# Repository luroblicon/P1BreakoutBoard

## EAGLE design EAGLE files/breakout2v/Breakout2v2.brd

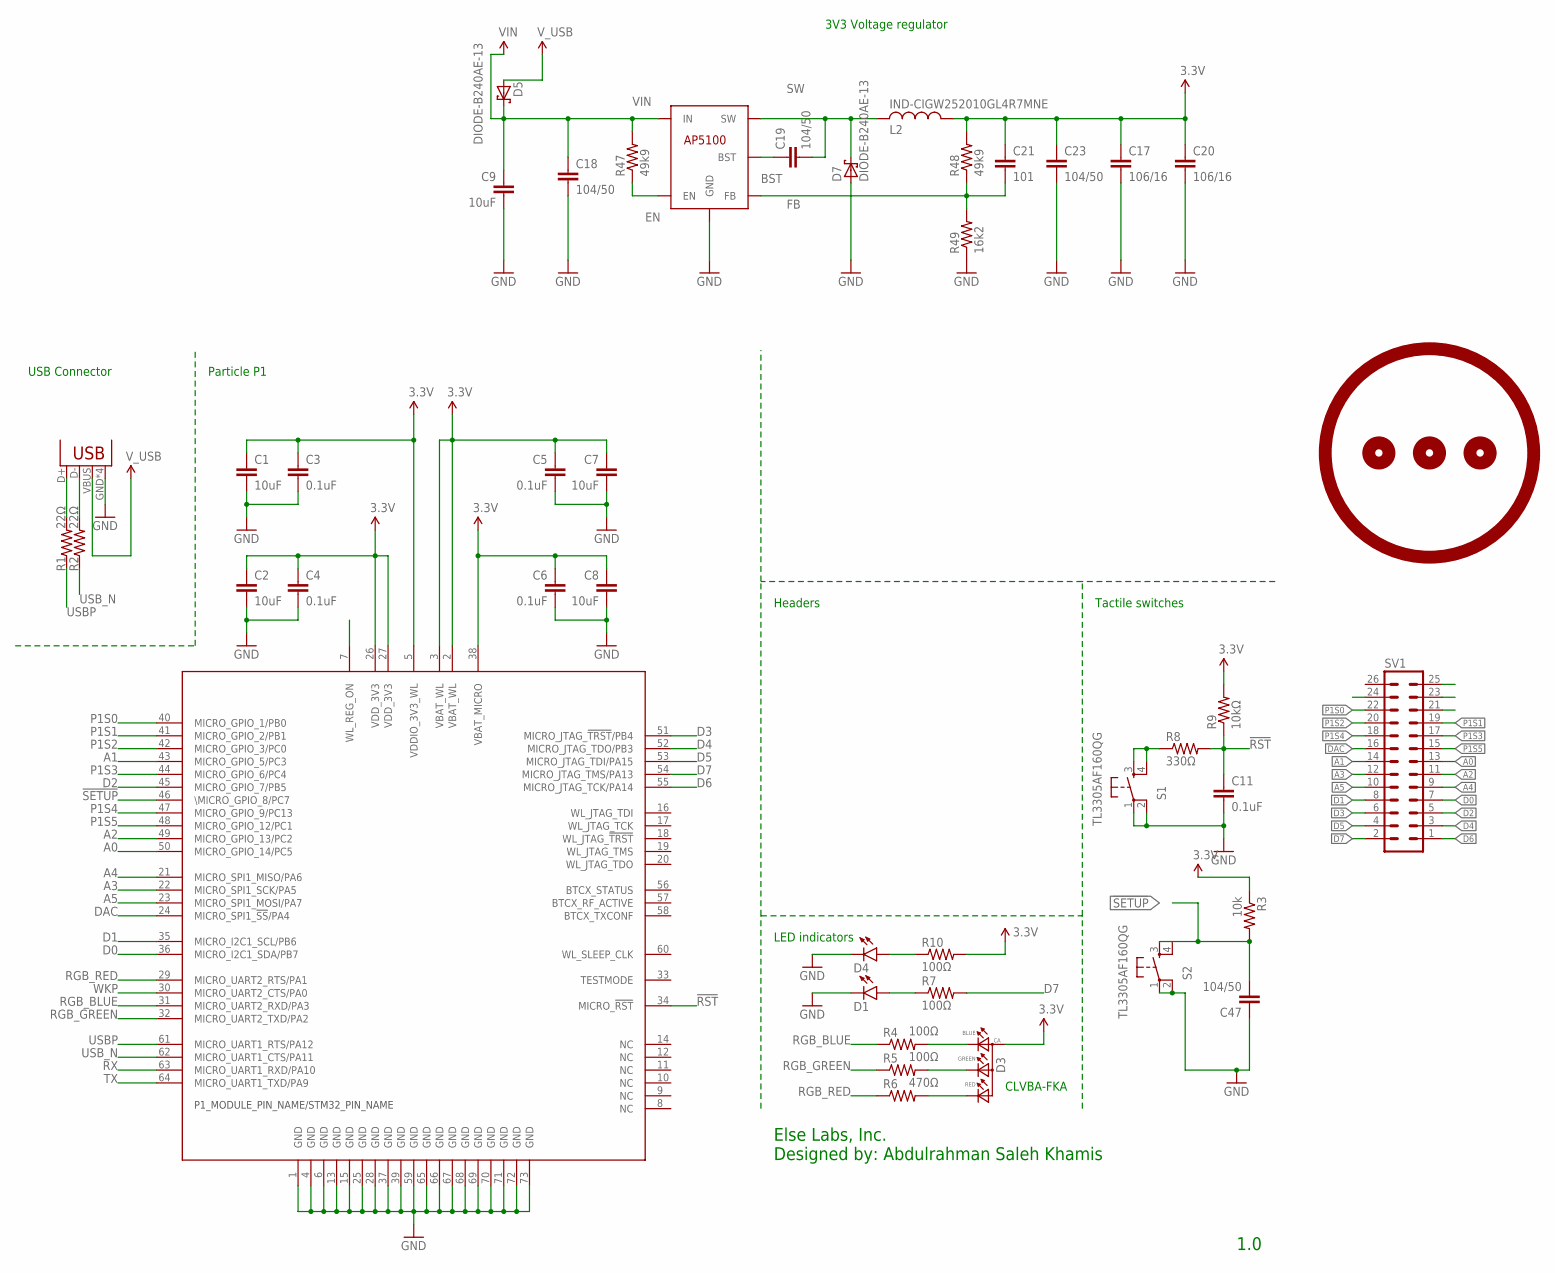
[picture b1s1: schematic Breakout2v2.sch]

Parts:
C1, C2, C7, C8, C9: 10uF; 0805
C3, C4, C5, C6, C11: 0.1uF; 0805
C17, C20: 106/16; C0805
C18, C19, C23, C47: 104/50; C0603
C21: 101; C0603
D1, D4: LED0603; LED-0603
D3: CLVBA-FKAPLCC; 4-PLCC
D5, D7: DIODE-B240AE-13; DO-214AC
IC5: SMSP-BUCK-AP5100; SOT23-6
JP1: USBUSB-MICROB-SLOT-HOLE; USB-MICROB-SLOT-HOLE
L2: IND-CIGW252010GL4R7MNE; L2520
R1, R2: 22Ω; 0805
R3: 10k; R0603
R4, R5, R7, R10: 100Ω; 0805
R6: 470Ω; 0805
R8: 330Ω; 0805
R9: 10kΩ; 0805
R47, R48: 49k9; R0603
R49: 16k2; R0603
S1, S2: TL3305AF160QG; TACTILE_SWITCH_SMD_4.5X4.5MM
SV1: MA13-2
U$1: LOGO
UC1: P1; WM-N-BM-14

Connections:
3.3V: C1.1, C2.1, C3.1, C4.1, C5.1, C6.1, C7.1, C8.1, C17.1, C20.1, C21.1, C23.1, D3.2 (ANODE), L2.P$1 (1), R3.1, R9.2, R10.2, R48.2, UC1.2 (VBAT_WL), UC1.3 (VBAT_WL), UC1.5 (VDDIO_3V3_WL), UC1.26 (VDD_3V3), UC1.27 (VDD_3V3), UC1.38 (VBAT_MICRO)
!RST: C11.1, R8.2, R9.1, UC1.34 (MICRO_!RST!)
!SETUP: C47.2, R3.2, S2.3, S2.4, UC1.46 (\MICRO_GPIO_8/PC7)
A0: SV1.13, UC1.50 (MICRO_GPIO_14/PC5)
A1: SV1.14, UC1.43 (MICRO_GPIO_5/PC3)
A2: SV1.11, UC1.49 (MICRO_GPIO_13/PC2)
A3: SV1.12, UC1.22 (MICRO_SPI1_SCK/PA5)
A4: SV1.9, UC1.21 (MICRO_SPI1_MISO/PA6)
A5: SV1.10, UC1.23 (MICRO_SPI1_MOSI/PA7)
BLR: D3.3 (BLUE), R4.2
BST: C19.1, IC5.1 (BST)
D0: SV1.7, UC1.36 (MICRO_I2C1_SDA/PB7)
D1: SV1.8, UC1.35 (MICRO_I2C1_SCL/PB6)
D2: SV1.5, UC1.45 (MICRO_GPIO_7/PB5)
D3: SV1.6, UC1.51 (MICRO_JTAG_!TRST!/PB4)
D4: SV1.3, UC1.52 (MICRO_JTAG_TDO/PB3)
D5: SV1.4, UC1.53 (MICRO_JTAG_TDI/PA15)
D6: SV1.1, UC1.55 (MICRO_JTAG_TCK/PA14)
D7: R7.2, SV1.2, UC1.54 (MICRO_JTAG_TMS/PA13)
DAC: SV1.16, UC1.24 (MICRO_SPI1_!SS!/PA4)
EN: IC5.4 (EN), R47.1
FB: C21.2, IC5.3 (FB), R48.1, R49.2
GND: C1.2, C2.2, C3.2, C4.2, C5.2, C6.2, C7.2, C8.2, C9.2, C11.2, C17.2, C18.2, C20.2, C23.2, C47.1, D1.C, D4.C, D7.A, IC5.2 (GND), JP1.GND, JP1.P$1 (GND), JP1.P$2 (GND), JP1.P$3 (GND), R49.1, S1.1, S1.2, S2.1, S2.2, UC1.1 (GND), UC1.4 (GND), UC1.6 (GND), UC1.13 (GND), UC1.15 (GND), UC1.25 (GND), UC1.28 (GND), UC1.37 (GND), UC1.39 (GND), UC1.59 (GND), UC1.65 (GND), UC1.66 (GND), UC1.67 (GND), UC1.68 (GND), UC1.69 (GND), UC1.70 (GND), UC1.71 (GND), UC1.72 (GND), UC1.73 (GND)
GRR: D3.4 (GREEN), R5.2
unnamed: JP1.D+, R1.2
unnamed: JP1.D-, R2.2
unnamed: D1.A, R7.1
unnamed: R8.1, S1.3, S1.4
unnamed: D4.A, R10.1
P1S0: SV1.22, UC1.40 (MICRO_GPIO_1/PB0)
P1S1: SV1.19, UC1.41 (MICRO_GPIO_2/PB1)
P1S2: SV1.20, UC1.42 (MICRO_GPIO_3/PC0)
P1S3: SV1.17, UC1.44 (MICRO_GPIO_6/PC4)
P1S4: SV1.18, UC1.47 (MICRO_GPIO_9/PC13)
P1S5: SV1.15, UC1.48 (MICRO_GPIO_12/PC1)
RER: D3.1 (RED), R6.2
RGB_BLUE: R4.1, UC1.31 (MICRO_UART2_RXD/PA3)
RGB_GREEN: R5.1, UC1.32 (MICRO_UART2_TXD/PA2)
RGB_RED: R6.1, UC1.29 (MICRO_UART2_RTS/PA1)
RX: UC1.63 (MICRO_UART1_RXD/PA10)
SW: C19.2, D7.C, IC5.6 (SW), L2.P$2 (2)
TX: UC1.64 (MICRO_UART1_TXD/PA9)
USBP: R1.1, UC1.61 (MICRO_UART1_RTS/PA12)
USB_N: R2.1, UC1.62 (MICRO_UART1_CTS/PA11)
VIN: C9.1, C18.1, D5.C, IC5.5 (IN), R47.2
V_USB: D5.A, JP1.VBUS
WKP: UC1.30 (MICRO_UART2_CTS/PA0)

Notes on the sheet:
CLVBA-FKA
USB Connector
Particle P1
3V3 Voltage regulator
Headers
Tactile switches
LED indicators
1.0
Else Labs, Inc. Designed by: Abdulrahman Saleh Khamis

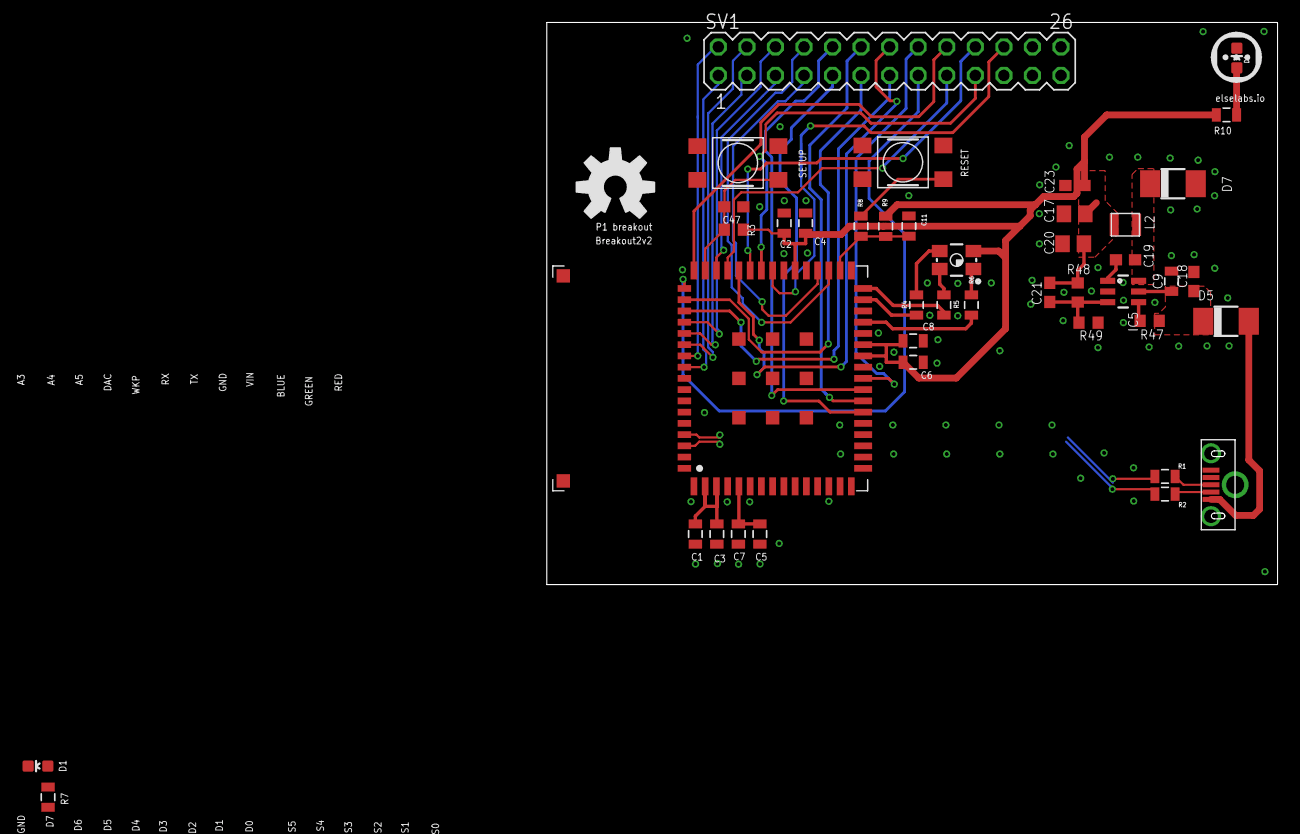
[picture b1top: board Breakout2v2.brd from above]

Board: 2 copper layers, 65.0 x 50.0 mm, 44 parts (0 on the bottom side), 44 nets.

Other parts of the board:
U$3: OSHW-LOGO-L

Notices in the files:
parts and their libraries:
Particle-Devices: Licensing: Designed by Particle.
SparkFun-Capacitors: Licensing: Creative Commons ShareAlike 4.0 International - https://creativecommons.org/licenses/by-sa/4.0
